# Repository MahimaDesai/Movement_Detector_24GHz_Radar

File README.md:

# Movement_Detector_24GHz_Radar
A 24 GHz radar sensor detects movements and sends detected signal to bandpass filter.
The 4th order Bandpass filter gives amplified signal as the output which in-turn is sent to the ADC.
PSOC calculates FFT of ADC data and sends it to MATLAB.
CFAR is used to set a threshold with which the probability of false alarm reduced.

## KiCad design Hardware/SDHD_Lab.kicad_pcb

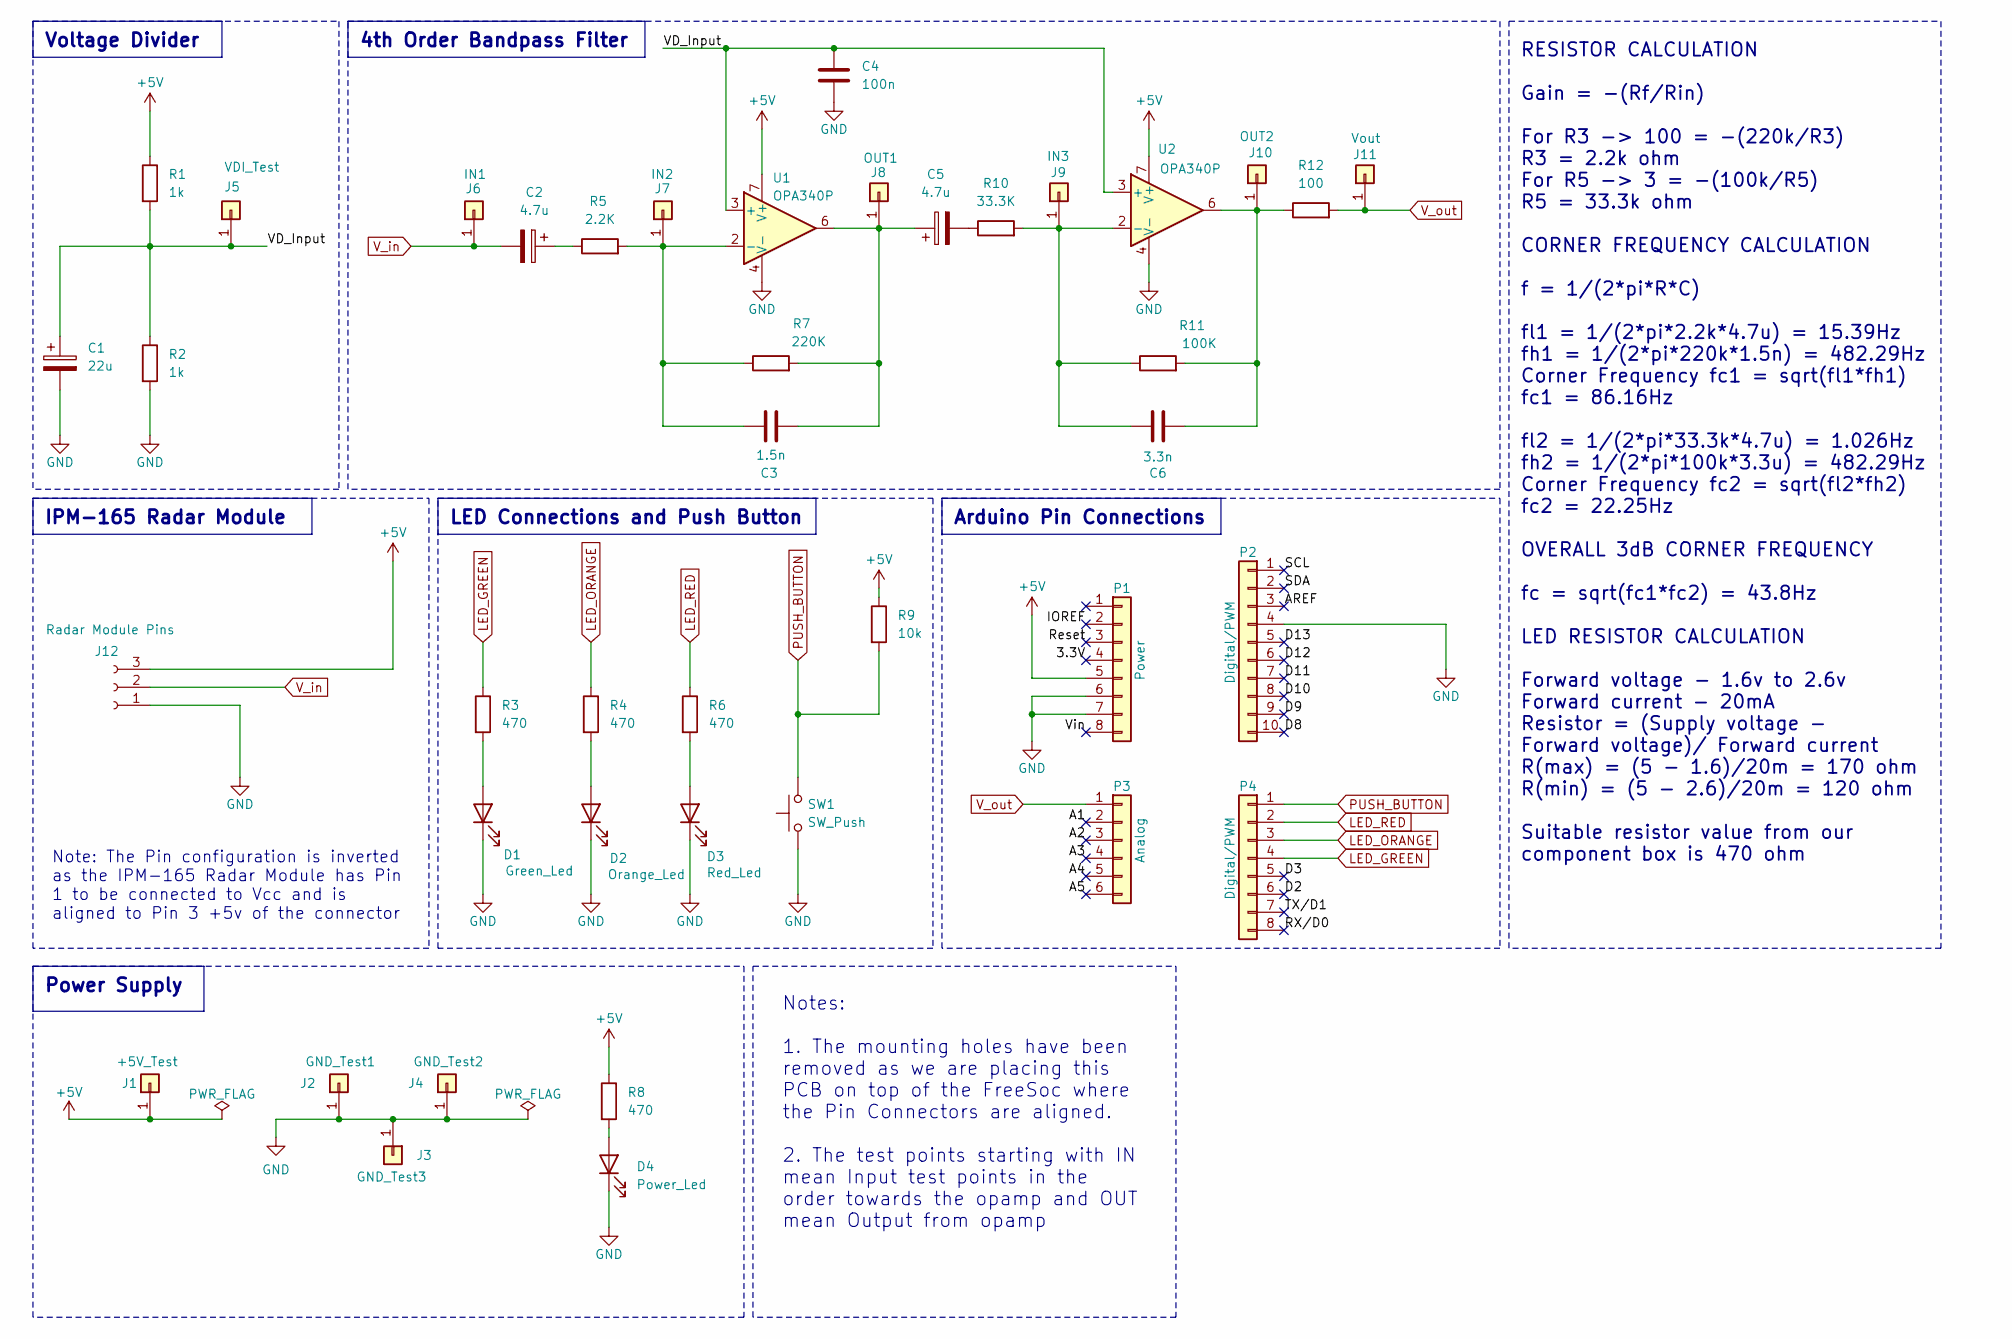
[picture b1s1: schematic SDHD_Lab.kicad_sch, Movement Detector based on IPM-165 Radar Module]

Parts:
C1: 22u; CP_Radial_D5.0mm_P2.50mm
C2, C5: 4.7u; CP_Radial_D6.3mm_P2.50mm
C3: 1.5n; C_Rect_L7.2mm_W7.2mm_P5.00mm_FKS2_FKP2_MKS2_MKP2
C4: 100n; C_Rect_L7.2mm_W2.5mm_P5.00mm_FKS2_FKP2_MKS2_MKP2
C6: 3.3n; C_Rect_L7.2mm_W7.2mm_P5.00mm_FKS2_FKP2_MKS2_MKP2
D1: Green_Led; LED_D5.0mm
D2: Orange_Led; LED_D5.0mm
D3: Red_Led; LED_D5.0mm
D4: Power_Led; LED_D5.0mm
J1: +5V_Test; PinHeader_1x01_P2.54mm_Vertical
J2: GND_Test1; PinHeader_1x01_P2.54mm_Vertical
J3: GND_Test3; PinHeader_1x01_P2.54mm_Vertical
J4: GND_Test2; PinHeader_1x01_P2.54mm_Vertical
J5: VDI_Test; PinHeader_1x01_P2.54mm_Vertical
J6: IN1; PinHeader_1x01_P2.54mm_Vertical
J7: IN2; PinHeader_1x01_P2.54mm_Vertical
J8: OUT1; PinHeader_1x01_P2.54mm_Vertical
J9: IN3; PinHeader_1x01_P2.54mm_Vertical
J10: OUT2; PinHeader_1x01_P2.54mm_Vertical
J11: Vout; PinHeader_1x01_P2.54mm_Vertical
J12: Radar Module Pins; PinSocket_1x03_P2.54mm_Horizontal
P1: Power; PinHeader_1x08_P2.54mm_Vertical
P2: Digital/PWM; PinHeader_1x10_P2.54mm_Vertical
P3: Analog; PinHeader_1x06_P2.54mm_Vertical
P4: Digital/PWM; PinHeader_1x08_P2.54mm_Vertical
R1, R2: 1k; R_Axial_DIN0207_L6.3mm_D2.5mm_P10.16mm_Horizontal
R3, R4, R6, R8: 470; R_Axial_DIN0207_L6.3mm_D2.5mm_P10.16mm_Horizontal
R5: 2.2K; R_Axial_DIN0207_L6.3mm_D2.5mm_P10.16mm_Horizontal
R7: 220K; R_Axial_DIN0207_L6.3mm_D2.5mm_P10.16mm_Horizontal
R9: 10k; R_Axial_DIN0207_L6.3mm_D2.5mm_P10.16mm_Horizontal
R10: 33.3K; R_Axial_DIN0207_L6.3mm_D2.5mm_P10.16mm_Horizontal
R11: 100K; R_Axial_DIN0207_L6.3mm_D2.5mm_P10.16mm_Horizontal
R12: 100; R_Axial_DIN0207_L6.3mm_D2.5mm_P10.16mm_Horizontal
SW1: SW_Push; SW_PUSH_6mm_H7.3mm
U1, U2: OPA340P; DIP-8_W7.62mm

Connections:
+5V: J1.1, J12.3, P1.5, R1.1, R8.1, R9.1, U1.7 (V+), U2.7 (V+)
/3.3V: P1.4
/A1: P3.2
/A2: P3.3
/A3: P3.4
/A4: P3.5
/A5: P3.6
/AREF: P2.3
/D2: P4.6
/D3: P4.5
/D8: P2.10
/D9: P2.9
/D10: P2.8
/D11: P2.7
/D12: P2.6
/D13: P2.5
/IOREF: P1.2
/RX/D0: P4.8
/Reset: P1.3
/SCL: P2.1
/SDA: P2.2
/TX/D1: P4.7
/VD_Input: C1.1, C4.1, J5.1, R1.2, R2.1, U1.3 (+), U2.3 (+)
/Vin: P1.8
GND: C1.2, C4.2, D1.1 (K), D2.1 (K), D3.1 (K), D4.1 (K), J2.1, J3.1, J4.1, J12.1, P1.6, P1.7, P2.4, R2.2, SW1.1, U1.4 (V-), U2.4 (V-)
LED_GREEN: P4.4, R3.1
LED_ORANGE: P4.3, R4.1
LED_RED: P4.2, R6.1
unnamed: C2.1, R5.1
unnamed: C5.2, R10.1
unnamed: D1.2 (A), R3.2
unnamed: D2.2 (A), R4.2
unnamed: D3.2 (A), R6.2
unnamed: D4.2 (A), R8.2
unnamed 34: C3.1, J7.1, R5.2, R7.1, U1.2 (-); also elsewhere on the board
unnamed 35: C3.2, C5.1, J8.1, R7.2, U1.6; also elsewhere on the board
unnamed: C6.1, J9.1, R10.2, R11.1, U2.2 (-)
unnamed: C6.2, J10.1, R11.2, R12.1, U2.6
PUSH_BUTTON: P4.1, R9.2, SW1.2
V_in: C2.2, J6.1, J12.2
V_out: J11.1, P3.1, R12.2

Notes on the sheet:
Power Supply
4th Order Bandpass Filter
IPM-165 Radar Module
LED Connections and Push Button
Voltage Divider
Note: The Pin configuration is inverted as the IPM-165 Radar Module has Pin 1 to be connected to Vcc and is aligned to Pin 3 +5v of the connector
Notes: 1. The mounting holes have been removed as we are placing this PCB on top of the FreeSoc where the Pin Connectors are aligned. 2. The test points starting with IN mean Input test points in the order towards the opamp and OUT mean Output from opamp
Arduino Pin Connections
RESISTOR CALCULATION Gain = -(Rf/Rin) For R3 -> 100 = -(220k/R3) R3 = 2.2k ohm For R5 -> 3 = -(100k/R5) R5 = 33.3k ohm CORNER FREQUENCY CALCULATION f = 1/(2*pi*R*C) fl1 = 1/(2*pi*2.2k*4.7u) = 15.39Hz fh1 = 1/(2*pi*220k*1.5n) = 482.29Hz Corner Frequency fc1 = sqrt(fl1*fh1) fc1 = 86.16Hz fl2 = 1/(2*p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

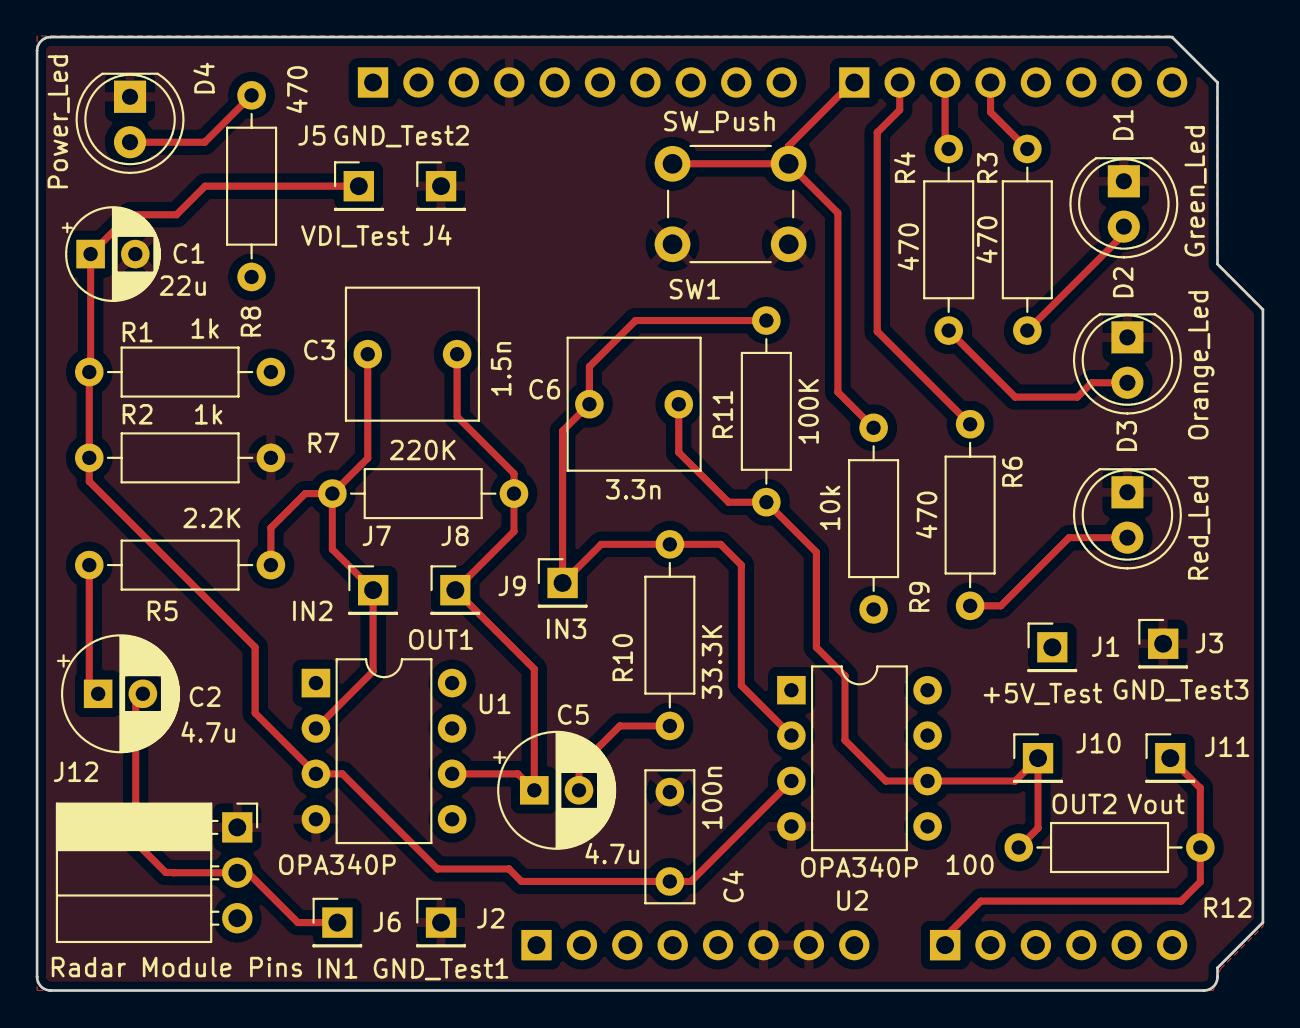
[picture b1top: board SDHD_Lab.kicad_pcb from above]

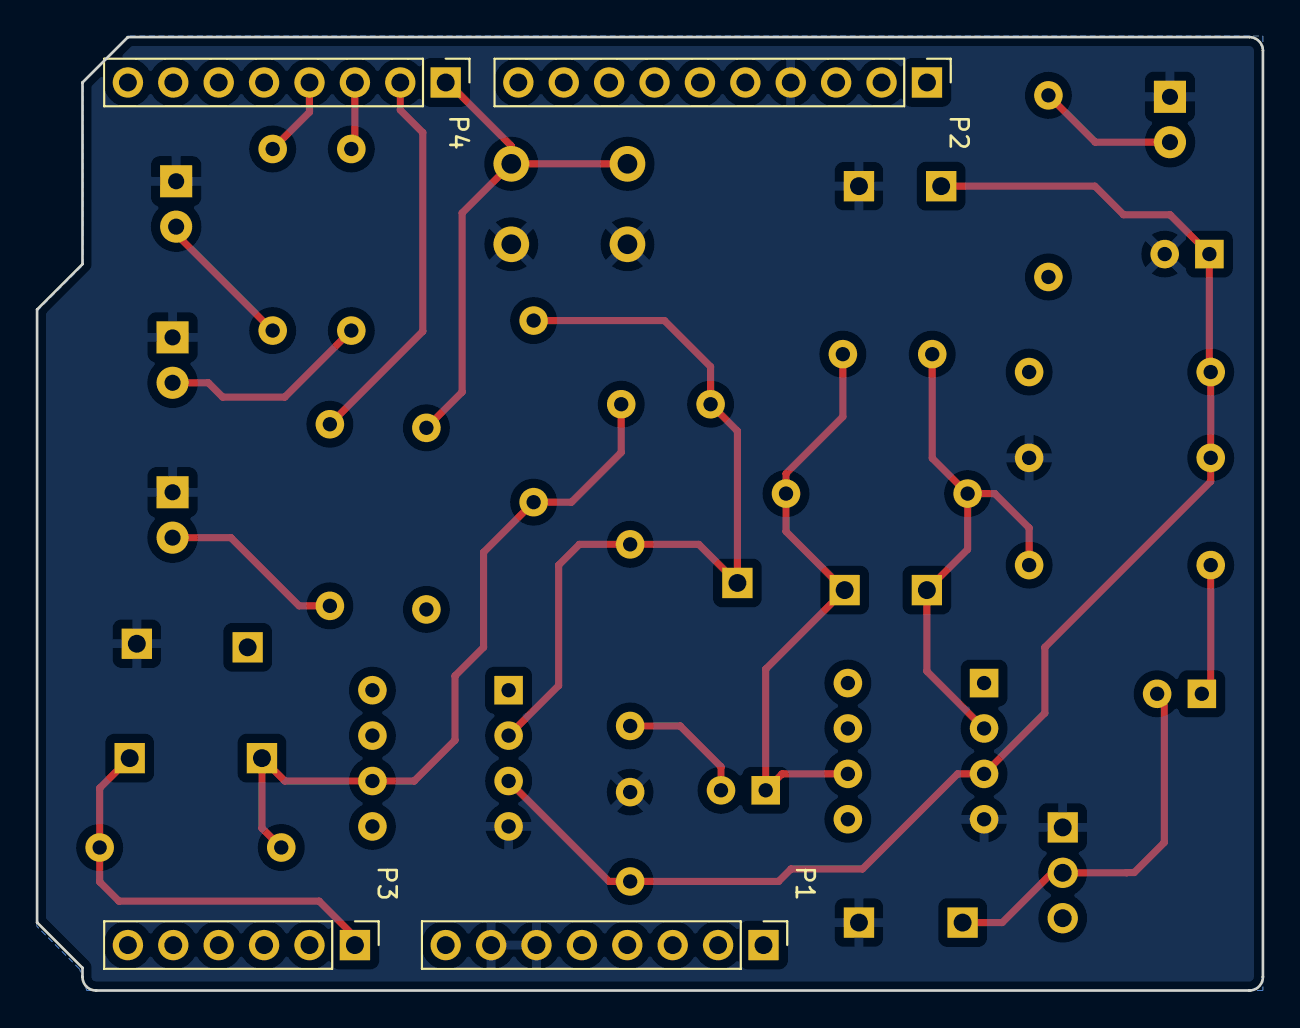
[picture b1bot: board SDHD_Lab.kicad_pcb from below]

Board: 4 copper layers, 68.6 x 53.3 mm, 41 parts (4 on the bottom side), 19 nets.

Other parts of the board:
R7 : 220K; R_Axial_DIN0207_L6.3mm_D2.5mm_P10.16mm_Horizontal

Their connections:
unnamed 34: R7.1; also elsewhere on the board
unnamed 35: R7.2; also elsewhere on the board

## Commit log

2024-08-13 Create Hardware
2024-08-13 Create temp
2024-08-13 PSoC_Project_Code
2024-08-13 MATLAB
2024-08-14 adding software.cydsn folder
